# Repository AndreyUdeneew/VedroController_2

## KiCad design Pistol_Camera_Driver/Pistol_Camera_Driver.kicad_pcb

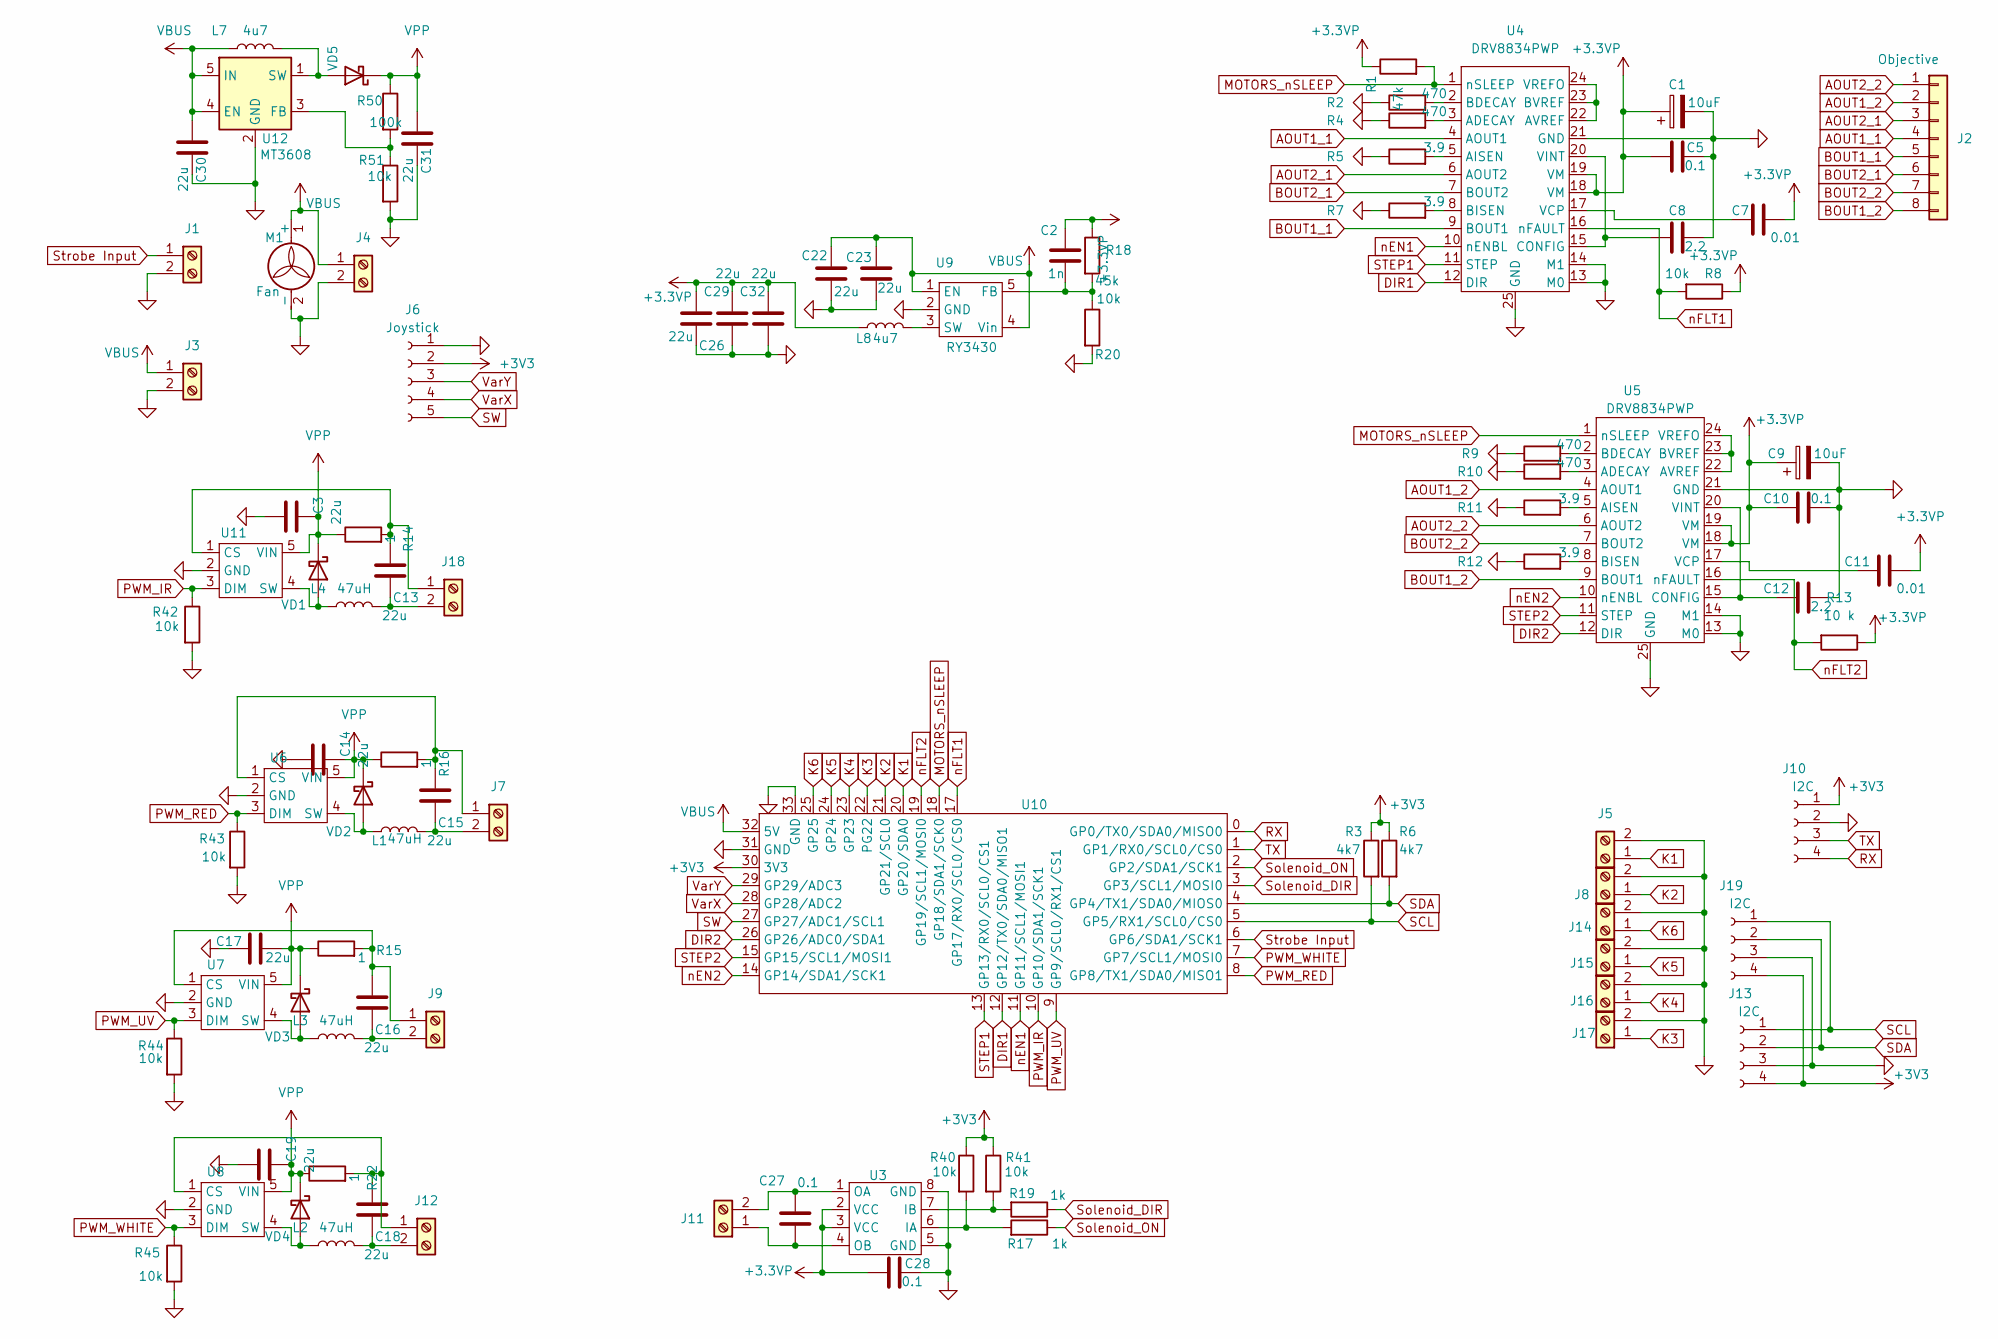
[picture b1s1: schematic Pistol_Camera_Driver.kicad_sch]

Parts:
C1, C9: 10uF; CP_Radial_D5.0mm_P2.00mm
C2: 1n; C_0603_1608Metric_Pad1.08x0.95mm_HandSolder
C3, C13, C14, C15, C16, C17, C18, C19, C22, C23, C26, C29, C32: 22u; C_0805_2012Metric_Pad1.18x1.45mm_HandSolder
C5, C10, C27, C28: 0.1; C_0603_1608Metric_Pad1.08x0.95mm_HandSolder
C7, C11: 0.01; C_0603_1608Metric_Pad1.08x0.95mm_HandSolder
C8, C12: 2.2; C_0603_1608Metric_Pad1.08x0.95mm_HandSolder
C30, C31: 22u; C_0603_1608Metric_Pad1.08x0.95mm_HandSolder
J1, J3, J4, J5, J7, J8, J9, J12, J14, J15, J16, J17, J18: Screw_Terminal_01x02; JST_XH_B2B-XH-A_1x02_P2.50mm_Vertical
J2: Objective; PinSocket_1x08_P1.27mm_Vertical
J6: Joystick; JST_XH_B5B-XH-A_1x05_P2.50mm_Vertical
J10: I2C; PinSocket_1x04_P2.54mm_Vertical
J11: Screw_Terminal_01x02; PinSocket_1x02_P1.27mm_Vertical
J13, J19: I2C; JST_XH_B4B-XH-A_1x04_P2.50mm_Vertical
L1, L2, L3, L4: 47uH; L_APV_ANR5045
L7, L8: 4u7; L_Chilisin_BMRx00040412
M1: Fan
R1: 47k; R_0603_1608Metric_Pad0.98x0.95mm_HandSolder
R2, R4, R9, R10: 470; R_0603_1608Metric_Pad0.98x0.95mm_HandSolder
R3, R6: 4k7; R_0603_1608Metric_Pad0.98x0.95mm_HandSolder
R5, R7, R11, R12: 3.9; R_0603_1608Metric_Pad0.98x0.95mm_HandSolder
R8, R20, R40, R41, R42, R43, R44, R45, R51: 10k; R_0603_1608Metric_Pad0.98x0.95mm_HandSolder
R13: 10 k; R_0603_1608Metric_Pad0.98x0.95mm_HandSolder
R14, R15, R16, R22: 1; R_0603_1608Metric_Pad0.98x0.95mm_HandSolder
R17, R19: 1k; R_0603_1608Metric_Pad0.98x0.95mm_HandSolder
R18: 45k; R_0603_1608Metric_Pad0.98x0.95mm_HandSolder
R50: 100k; R_0603_1608Metric_Pad0.98x0.95mm_HandSolder
U3: SOIC-8_3.9x4.9mm_P1.27mm
U4, U5: DRV8834PWP
U6, U7, U8, U11: SOT-89-5
U9: RY3430; SOT-23-5
U10: RP2040Zero
U12: MT3608; SOT-23-6
VD1, VD2, VD3, VD4, VD5: CDBA3100-HF; D_SOD-123

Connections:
+3.3VP: C1.1, C2.1, C5.2, C7.2, C9.1, C10.1, C11.2, C26.1, C28.2, C29.2, C32.2, L8.1, R1.1, R8.1, R13.1, R18.1, U3.2 (VCC), U3.3 (VCC), U4.18 (VM), U4.19 (VM), U5.18 (VM), U5.19 (VM)
+3V3: J6.2, J10.1, J13.4, J19.4, R3.1, R6.1, R40.1, R41.1, U10.30 (3V3)
AOUT1_1: J2.4, U4.4 (AOUT1)
AOUT1_2: J2.2, U5.4 (AOUT1)
AOUT2_1: J2.3, U4.6 (AOUT2)
AOUT2_2: J2.1, U5.6 (AOUT2)
BOUT1_1: J2.5, U4.9 (BOUT1)
BOUT1_2: J2.8, U5.9 (BOUT1)
BOUT2_1: J2.6, U4.7 (BOUT2)
BOUT2_2: J2.7, U5.7 (BOUT2)
DIR1: U4.12 (DIR), U10.12 (GP12/TX0/SDA0/MISO1)
DIR2: U5.12 (DIR), U10.26 (GP26/ADC0/SDA1)
GND: C1.2, C3.1, C5.1, C8.2, C9.2, C10.2, C12.2, C14.1, C17.1, C19.1, C22.2, C23.1, C26.2, C28.1, C29.1, C30.2, C31.2, C32.1, J1.2, J3.2, J4.2, J5.2, J6.1, J8.2, J10.2, J13.3, J14.2, J15.2, J16.2, J17.2, J19.3, M1.2 (-), R2.1, R4.1, R5.1, R7.1, R9.1, R10.1, R11.1, R12.1, R20.2, R42.2, R43.2, R44.2, R45.2, R51.2, U3.5 (GND), U3.8 (GND), U4.13 (M0), U4.14 (M1), U4.21 (GND), U4.25 (GND), U5.13 (M0), U5.14 (M1), U5.21 (GND), U5.25 (GND), U6.2 (GND), U7.2 (GND), U8.2 (GND), U9.2 (GND), U10.31 (GND), U10.33 (GND), U11.2 (GND), U12.2 (GND)
K1: J5.1, U10.20 (GP20/SDA0)
K2: J8.1, U10.21 (GP21/SCL0)
K3: J17.1, U10.22 (PG22)
K4: J16.1, U10.23 (GP23)
K5: J15.1, U10.24 (GP24)
K6: J14.1, U10.25 (GP25)
MOTORS_nSLEEP: R1.2, U4.1 (nSLEEP), U5.1 (nSLEEP), U10.18 (GP18/SDA1/SCK0)
unnamed: C15.1, J7.1, R16.2, U6.1 (CS)
unnamed: C15.2, J7.2, L1.2
unnamed: C16.1, J9.1, R15.2, U7.1 (CS)
unnamed: C16.2, J9.2, L3.2
unnamed: C27.2, J11.1, U3.4 (OB)
unnamed: C27.1, J11.2, U3.1 (OA)
unnamed: C18.1, J12.1, R22.2, U8.1 (CS)
unnamed: C18.2, J12.2, L2.2
unnamed: C13.1, J18.1, R14.2, U11.1 (CS)
unnamed: C13.2, J18.2, L4.2
unnamed: R17.2, R40.2, U3.6 (IA)
unnamed: R19.2, R41.2, U3.7 (IB)
unnamed: R4.2, U4.3 (ADECAY)
unnamed: R5.2, U4.5 (AISEN)
unnamed: U4.22 (AVREF), U4.23 (BVREF), U4.24 (VREFO)
unnamed: R2.2, U4.2 (BDECAY)
unnamed: R7.2, U4.8 (BISEN)
unnamed: C8.1, U4.15 (CONFIG), U4.20 (VINT)
unnamed: C7.1, U4.17 (VCP)
unnamed: R10.2, U5.3 (ADECAY)
unnamed: R11.2, U5.5 (AISEN)
unnamed: U5.22 (AVREF), U5.23 (BVREF), U5.24 (VREFO)
unnamed: R9.2, U5.2 (BDECAY)
unnamed: R12.2, U5.8 (BISEN)
unnamed: C12.1, U5.15 (CONFIG), U5.20 (VINT)
unnamed: C11.1, U5.17 (VCP)
unnamed: L1.1, U6.4 (SW), VD2.2 (A)
unnamed: L3.1, U7.4 (SW), VD3.2 (A)
unnamed: L2.1, U8.4 (SW), VD4.2 (A)
unnamed: C2.2, R18.2, R20.1, U9.5 (FB)
unnamed: L8.2, U9.3 (SW)
unnamed: L4.1, U11.4 (SW), VD1.2 (A)
unnamed: R50.2, R51.1, U12.3 (FB)
unnamed: L7.2, U12.1 (SW), VD5.2 (A)
PWM_IR: R42.1, U10.10 (GP10/SDA1/SCK1), U11.3 (DIM)
PWM_RED: R43.1, U6.3 (DIM), U10.8 (GP8/TX1/SDA0/MISO1)
PWM_UV: R44.1, U7.3 (DIM), U10.9 (GP9/SCL0/RX1/CS1)
PWM_WHITE: R45.1, U8.3 (DIM), U10.7 (GP7/SCL1/MOSI0)
RX: J10.4, U10.0 (GP0/TX0/SDA0/MISO0)
SCL: J13.1, J19.1, R3.2, U10.5 (GP5/RX1/SCL0/CS0)
SDA: J13.2, J19.2, R6.2, U10.4 (GP4/TX1/SDA0/MIOS0)
STEP1: U4.11 (STEP), U10.13 (GP13/RX0/SCL0/CS1)
STEP2: U5.11 (STEP), U10.15 (GP15/SCL1/MOSI1)
SW: J6.5, U10.27 (GP27/ADC1/SCL1)
Solenoid_DIR: R19.1, U10.3 (GP3/SCL1/MOSI0)
Solenoid_ON: R17.1, U10.2 (GP2/SDA1/SCK1)
Strobe Input: J1.1, U10.6 (GP6/SDA1/SCK1)
TX: J10.3, U10.1 (GP1/RX0/SCL0/CS0)
VBUS: C22.1, C23.2, C30.1, J3.1, J4.1, L7.1, M1.1 (+), U9.1 (EN), U9.4 (Vin), U10.32 (5V), U12.4 (EN), U12.5 (IN)
VPP: C3.2, C14.2, C17.2, C19.2, C31.1, R14.1, R15.1, R16.1, R22.1, R50.1, U6.5 (VIN), U7.5 (VIN), U8.5 (VIN), U11.5 (VIN), VD1.1 (K), VD2.1 (K), VD3.1 (K), VD4.1 (K), VD5.1 (K)
VarX: J6.4, U10.28 (GP28/ADC2)
VarY: J6.3, U10.29 (GP29/ADC3)
nEN1: U4.10 (nENBL), U10.11 (GP11/SCL1/MOSI1)
nEN2: U5.10 (nENBL), U10.14 (GP14/SDA1/SCK1)
nFLT1: R8.2, U4.16 (nFAULT), U10.17 (GP17/RX0/SCL0/CS0)
nFLT2: R13.2, U5.16 (nFAULT), U10.19 (GP19/SCL1/MOSI0)

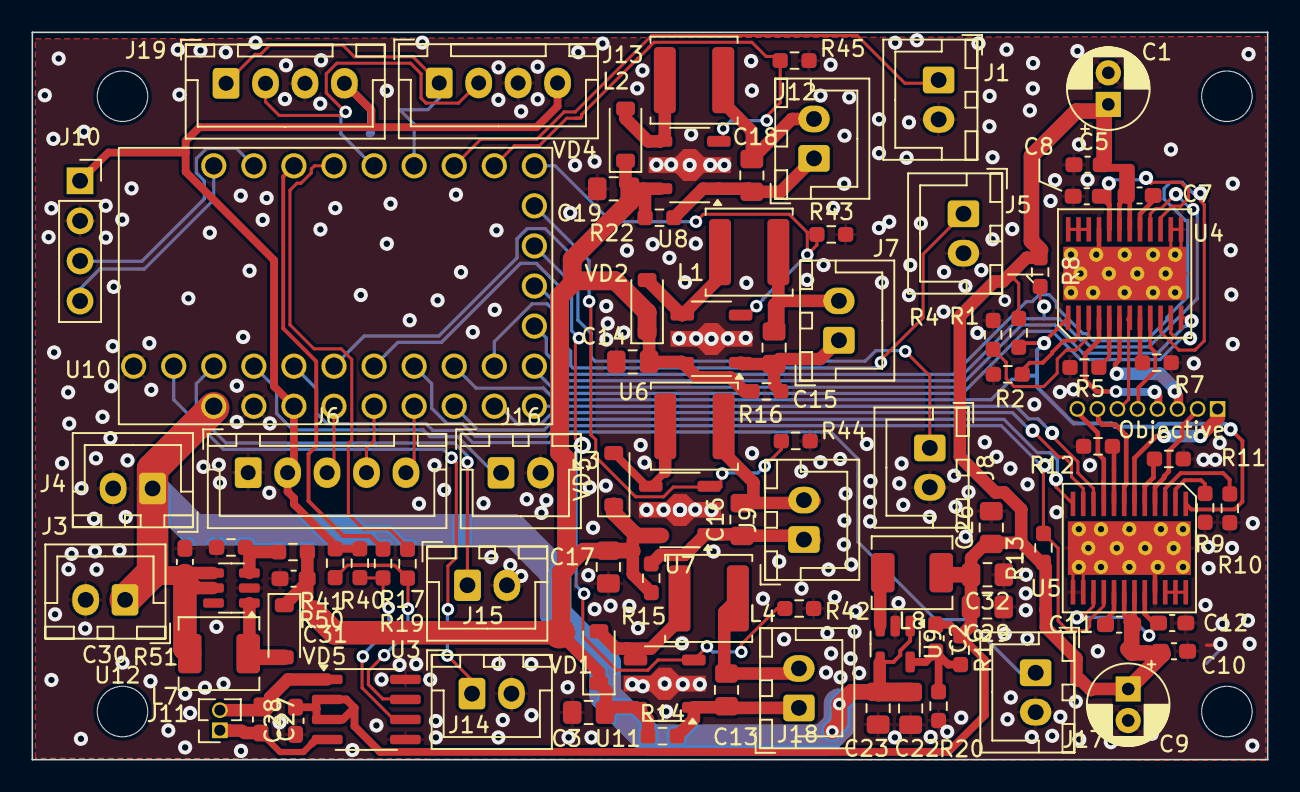
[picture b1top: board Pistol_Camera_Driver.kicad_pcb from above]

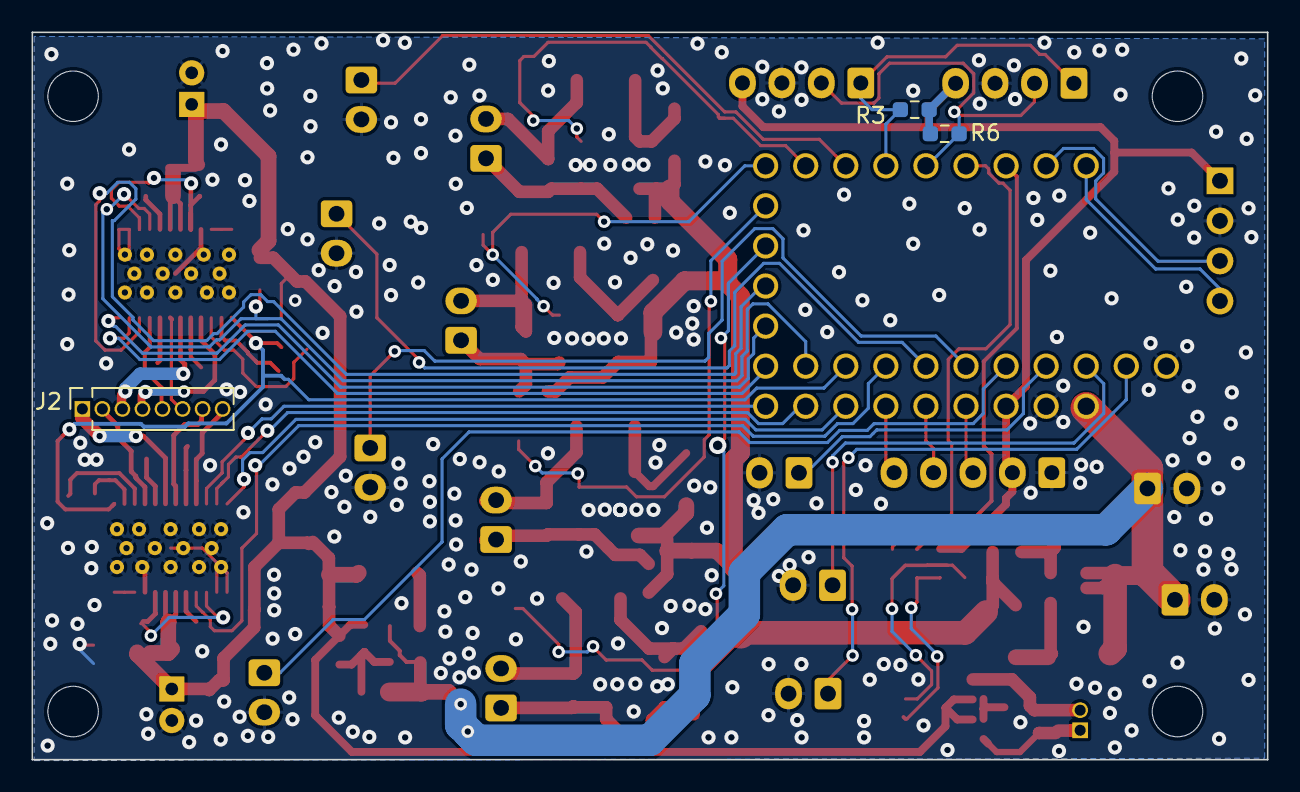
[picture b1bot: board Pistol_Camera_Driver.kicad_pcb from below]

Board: 2 copper layers, 78.3 x 46.1 mm, 95 parts (3 on the bottom side), 76 nets.

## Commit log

2025-01-18 v0.1 setp-up dc/dc was added
2025-01-18 v0.2 circuit was completed
2025-01-21 v0.3 actual state
2025-01-22 v0.4 draft decomposition completed
2025-01-22 v0.5 actual state
2025-01-23 v0.6 actual state
2025-01-23 v0.7 draft routung completed
2025-01-28 v0.8 compact BUCK converter for 3v3 was added
2025-01-30 v0.9 actual state
2025-01-31 v1.0 Draft routing and DRC completed
2025-01-31 v1.1 seems 2B working
